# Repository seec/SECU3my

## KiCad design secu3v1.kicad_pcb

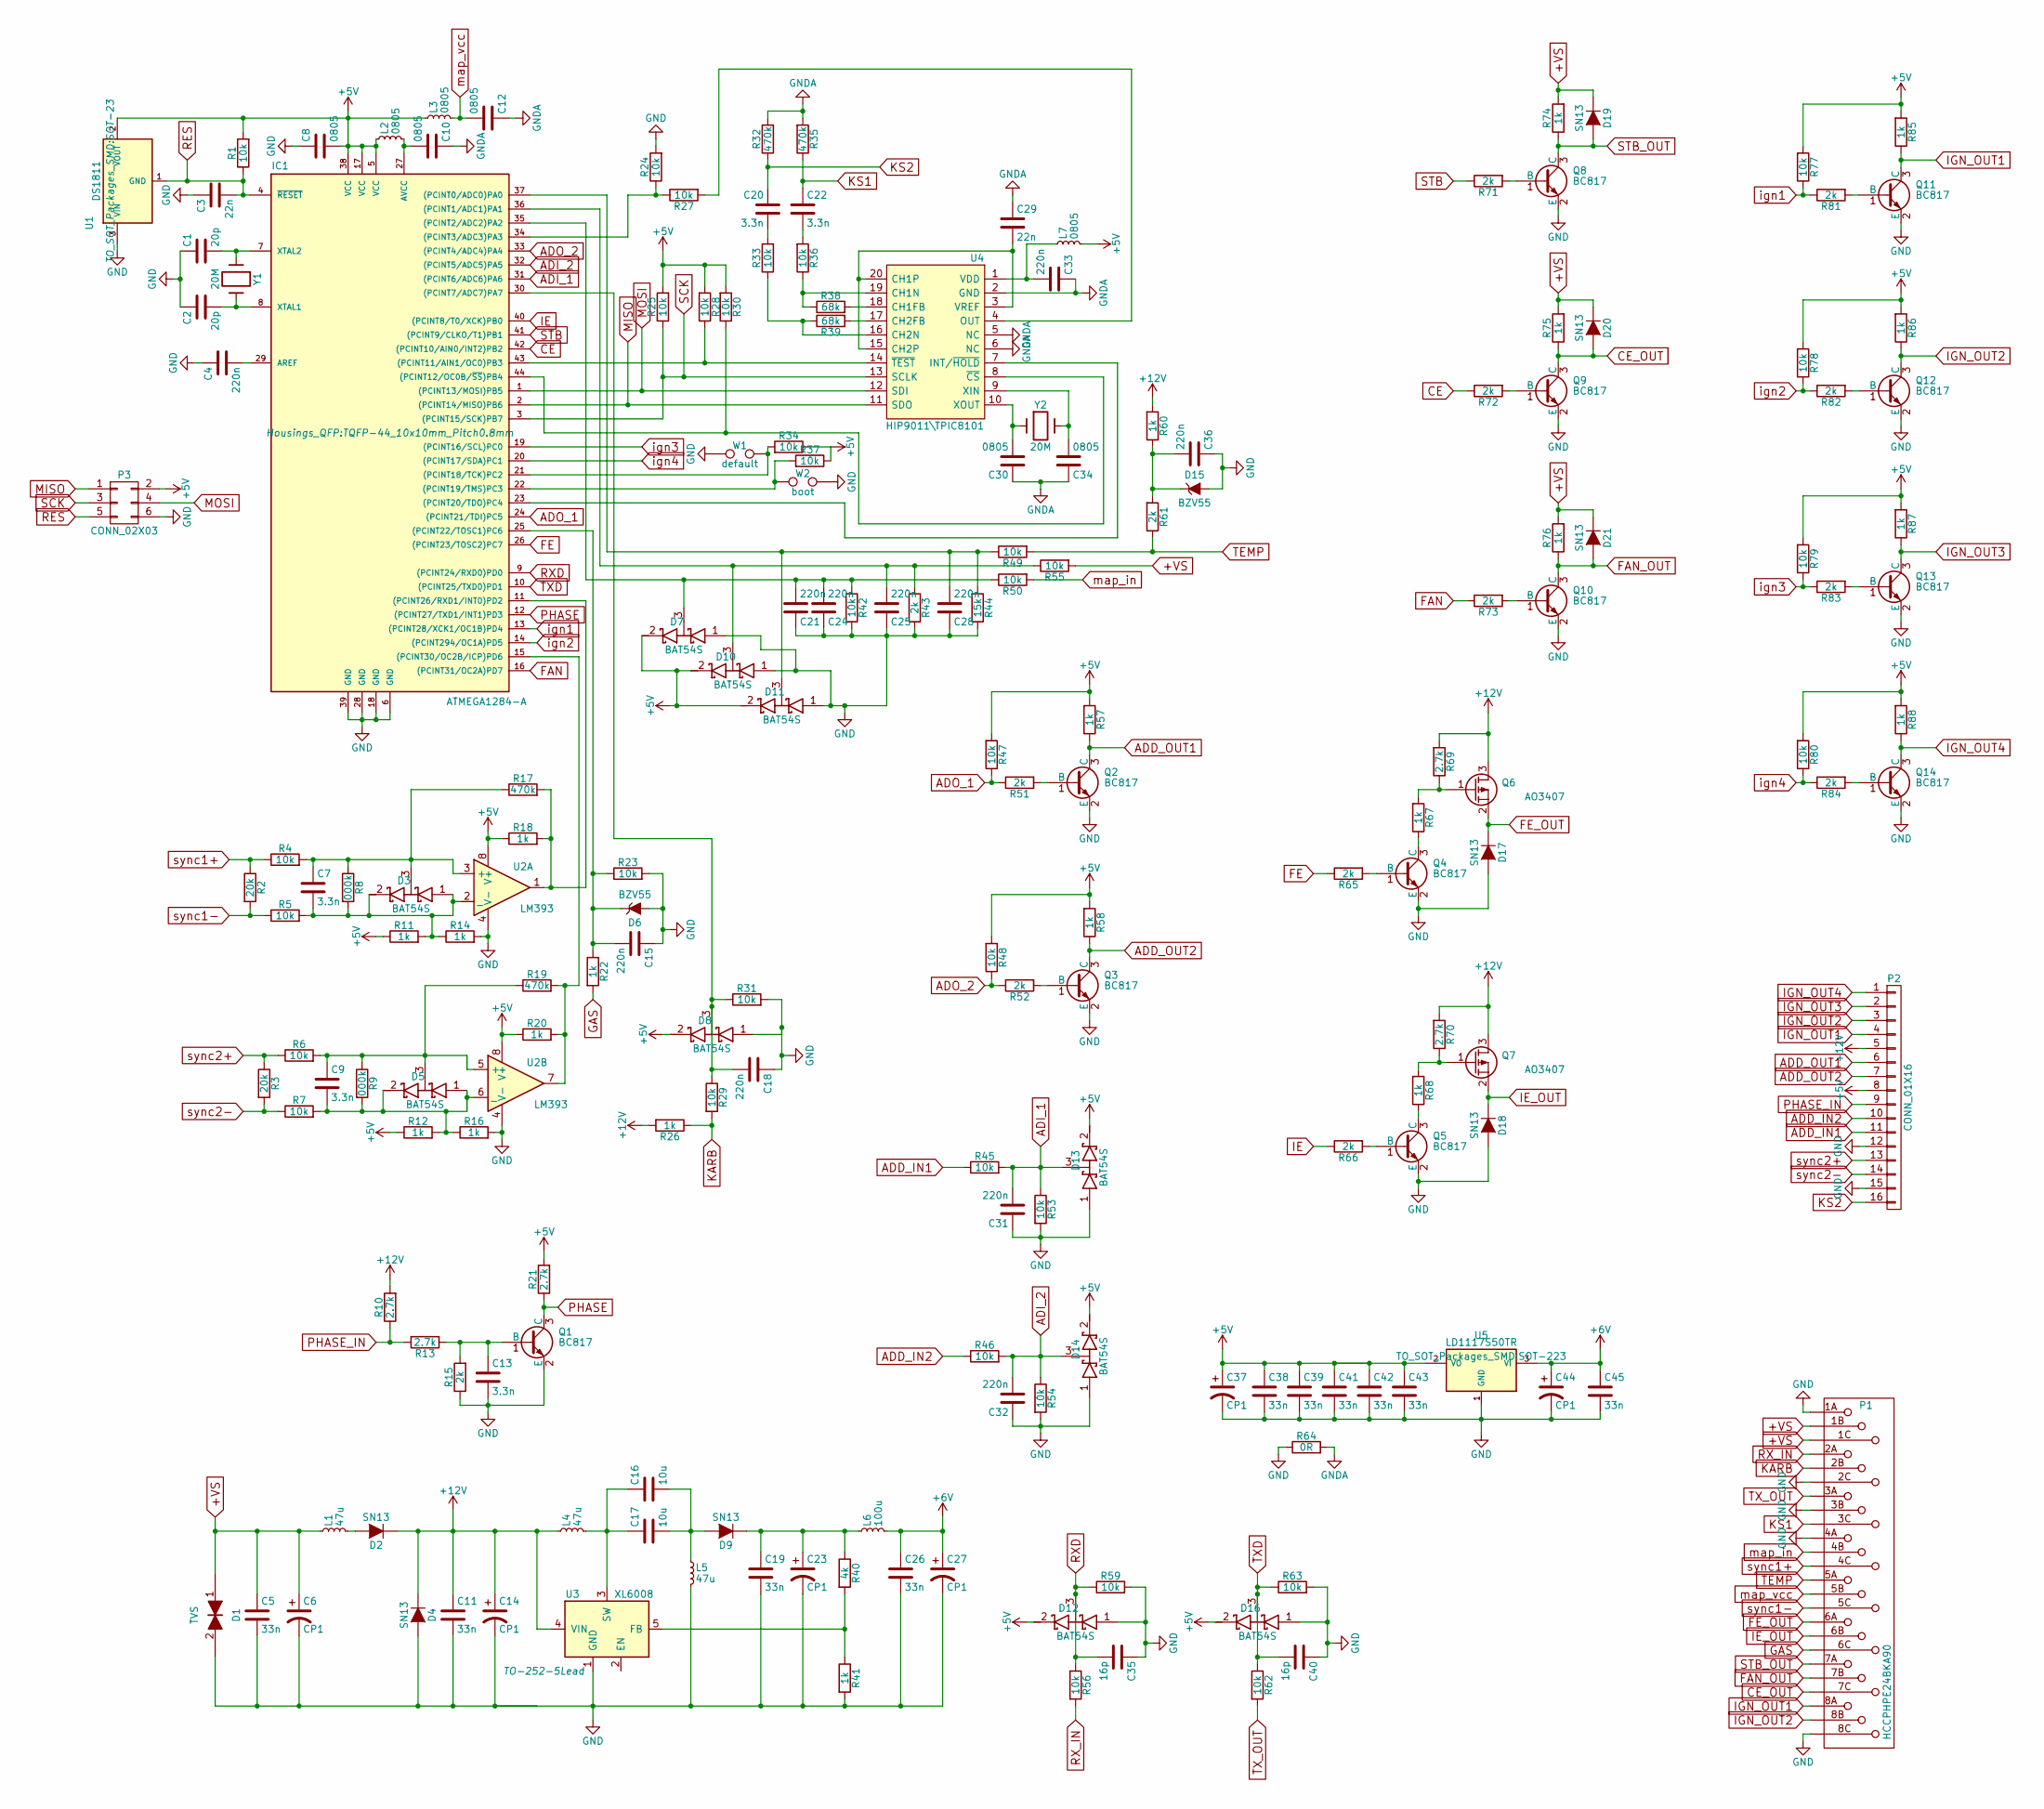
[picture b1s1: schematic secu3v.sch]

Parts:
C1, C2: 20p; C_0805
C3, C29: 22n; C_0805
C4, C15, C18, C21, C24, C25, C28, C31, C32, C33, C36: 220n; C_0805
C5, C11, C19, C26, C38, C39, C41, C42, C43, C45: 33n; C_0805
C6, C14: CP1; c_elec_8x10.5
C7, C9, C13, C20, C22: 3.3n; C_0805
C8, C10, C12, C30, C34: 0805; C_0805
C16, C17: 10u; C_0805
C23, C27, C37, C44: CP1; c_elec_6.3x4.5
C35, C40: 16p; C_0805
D1: TVS; SMA_Standard
D2, D4, D9, D17, D18, D19, D20, D21: SN13; SMA_Standard
D3, D5, D7, D8, D10, D11, D12, D13, D14, D16: BAT54S; SOT-23
D6, D15: BZV55; SMA_Standard
IC1: ATMEGA1284-A; TQFP-44_10x10mm_Pitch0.8mm
L1: 47u; Neosid_Inductor_SM-NE45_SMD1812
L2, L3, L7: 0805; Neosid_Inductor_SM-NE45_SMD1812
L4, L5: 47u; Choke_SMD_7.3x7.3_H4.5
L6: 100u; Neosid_Inductor_SM-NE45_SMD1812
P1: HCCPHPE24BKA90
P2: CONN_01X16; Pin_Header_Straight_1x16
P3: CONN_02X03; Pin_Header_Straight_2x03
Q1, Q2, Q3, Q4, Q5, Q8, Q9, Q10, Q11, Q12, Q13, Q14: BC817; SOT-23
Q6, Q7: AO3407; SOT-23
R1, R4, R5, R6, R7, R23, R24, R25, R27, R28, R29, R30, R31, R33, R34, R36, R37, R42, R45, R46, R47, R48, R49, R50, R53, R54, R55, R56, R59, R62, R63, R77, R78, R79, R80: 10k; R_0805
R2, R3: 20k; R_0805
R8, R9: 000k; R_0805
R10, R13, R21, R69, R70: 2.7k; R_0805
R11, R12, R14, R16, R18, R20, R22, R26, R41, R57, R58, R60, R67, R68, R74, R75, R76, R85, R86, R87, R88: 1k; R_0805
R15, R43, R51, R52, R61, R65, R66, R71, R72, R73, R81, R82, R83, R84: 2k; R_0805
R17, R19, R32, R35: 470k; R_0805
R38, R39: 68k; R_0805
R40: 4k; R_0805
R44: 15k; R_0805
R64: 0R; R_0805
U1: DS1811; SOT-23
U2: LM393; SOIC-8_3.9x4.9mm_Pitch1.27mm
U3: XL6008; TO-252-5Lead
U4: HIP9011\\TPIC8101; SOIC-20W_7.5x12.8mm_Pitch1.27mm
U5: LD1117S50TR; SOT-223
W1: default; Test_Point_2Pads
W2: boot; Test_Point_2Pads
Y1, Y2: 20M; Crystal_SMD_5032_2Pads

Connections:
+5V: C8.2, C37.1, C38.1, C39.1, C41.1, C42.1, C43.1, D7.2 (K), D8.2 (K), D10.2 (K), D11.2 (K), D12.2 (K), D13.2 (K), D14.2 (K), D16.2 (K), IC1.5 (VCC), IC1.17 (VCC), IC1.38 (VCC), L2.1, L3.1, L7.2, P2.8, P3.2, R1.2, R11.1, R12.1, R18.1, R20.1, R21.2, R25.2, R28.2, R30.2, R34.1, R37.1, R47.2, R48.2, R57.2, R58.2, R77.2, R78.2, R79.2, R80.2, R85.2, R86.2, R87.2, R88.2, U1.2 (VOUT), U2.8 (V+), U5.2 (VO)
+6V: C26.1, C27.1, C44.1, C45.1, L6.2, U5.3 (VI)
+12V: C11.1, C14.1, D2.1 (K), D4.1 (K), L4.1, P2.5, Q6.3 (D), Q7.3 (D), R10.2, R26.2, R60.2, R69.2, R70.2, U3.4 (VIN)
+VS: C5.1, C6.1, D1.1, D19.1 (K), D20.1 (K), D21.1 (K), L1.1, P1.1B, P1.1C, R55.2, R74.2, R75.2, R76.2
ADD_IN1: P2.11, R45.1
ADD_IN2: P2.10, R46.1
ADD_OUT1: P2.6, Q2.3 (C), R57.1
ADD_OUT2: P2.7, Q3.3 (C), R58.1
ADI_1: C31.2, D13.3 (common), IC1.31 ((PCINT6/ADC6)PA6), R45.2, R53.1
ADI_2: C32.2, D14.3 (common), IC1.32 ((PCINT5/ADC5)PA5), R46.2, R54.1
ADO_1: IC1.24 ((PCINT21/TDI)PC5), R47.1, R51.1
ADO_2: IC1.33 ((PCINT4/ADC4)PA4), R48.1, R52.1
CE: IC1.42 ((PCINT10/AIN0/INT2)PB2), R72.1
CE_OUT: D20.2 (A), P1.7C, Q9.3 (C), R75.1
FAN: IC1.16 ((PCINT31/OC2A)PD7), R73.1
FAN_OUT: D21.2 (A), P1.7B, Q10.3 (C), R76.1
FE: IC1.26 ((PCINT23/TOSC2)PC7), R65.1
FE_OUT: D17.1 (K), P1.6A, Q6.2 (S)
GAS: P1.6C, R22.2
GND: C1.1, C2.1, C3.1, C4.1, C5.2, C6.2, C8.1, C11.2, C13.2, C14.2, C15.1, C18.1, C19.2, C21.1, C23.2, C24.1, C25.1, C26.2, C27.2, C28.1, C31.1, C32.1, C35.1, C36.1, C37.2, C38.2, C39.2, C40.1, C41.2, C42.2, C43.2, C44.2, C45.2, D1.2, D4.2 (A), D6.2 (A), D7.1 (A), D8.1 (A), D10.1 (A), D11.1 (A), D12.1 (A), D13.1 (A), D14.1 (A), D15.2 (A), D16.1 (A), D17.2 (A), D18.2 (A), IC1.6 (GND), IC1.18 (GND), IC1.28 (GND), IC1.39 (GND), L5.2, P1.1A, P1.2C, P1.3B, P1.4A, P1.8C, P2.12, P2.15, P3.6, Q1.2 (E), Q2.2 (E), Q3.2 (E), Q4.2 (E), Q5.2 (E), Q8.2 (E), Q9.2 (E), Q10.2 (E), Q11.2 (E), Q12.2 (E), Q13.2 (E), Q14.2 (E), R14.2, R15.1, R16.2, R23.2, R24.2, R31.2, R41.2, R42.1, R43.1, R44.1, R53.2, R54.2, R59.2, R63.2, R64.1, U1.3 (VIN), U2.4 (V-), U3.1 (GND), U5.1 (GND), W1.1, W2.2; also elsewhere on the board
GNDA: C10.1, C12.1, C29.1, C30.1, C33.1, C34.1, R32.2, R35.2, R64.2, U4.2 (GND), U4.5 (NC), U4.6 (NC)
IE: IC1.40 ((PCINT8/T0/XCK)PB0), R66.1
IE_OUT: D18.1 (K), P1.6B, Q7.2 (S)
IGN_OUT1: P1.8A, P2.4, Q11.3 (C), R85.1
IGN_OUT2: P1.8B, P2.3, Q12.3 (C), R86.1
IGN_OUT3: P2.2, Q13.3 (C), R87.1
IGN_OUT4: P2.1, Q14.3 (C), R88.1
KARB: P1.2B, R26.1, R29.2
KS1: C22.1, P1.3C, R35.1
KS2: C20.1, P2.16, R32.1
MISO: IC1.2 ((PCINT14/MISO)PB6), P3.1, U4.11 (SDO)
MOSI: IC1.1 ((PCINT13/MOSI)PB5), P3.4, U4.12 (SDI)
unnamed: C1.2, IC1.7 (XTAL2), Y1.1
unnamed: C2.2, IC1.8 (XTAL1), Y1.2
unnamed: C4.2, IC1.29 (AREF)
unnamed: C7.1, D3.3 (common), R4.2, R8.1, R17.1, U2.3 (+)
unnamed: C7.2, D3.1 (A), D3.2 (K), R5.2, R8.2, R11.2, R14.1, U2.2 (_)
unnamed: C9.1, D5.3 (common), R6.2, R9.1, R19.1, U2.5 (+)
unnamed: C9.2, D5.1 (A), D5.2 (K), R7.2, R9.2, R12.2, R16.1, U2.6 (_)
unnamed: C10.2, IC1.27 (AVCC), L2.2
unnamed: C13.1, Q1.1 (B), R13.1, R15.2
unnamed: C15.2, D6.1 (K), IC1.25 ((PCINT22/TOSC1)PC6), R22.1, R23.1
unnamed: C16.1, C17.1, L4.2, U3.3 (SW)
unnamed: C16.2, C17.2, D9.2 (A), L5.1
unnamed: C18.2, D8.3 (common), IC1.30 ((PCINT7/ADC7)PA7), R29.1, R31.1
unnamed: C19.1, C23.1, D9.1 (K), L6.1, R40.1
unnamed: C20.2, R33.2
unnamed: C21.2, C24.2, D7.3 (common), IC1.35 ((PCINT2/ADC2)PA2), R42.2, R50.1
unnamed: C22.2, R36.2
unnamed: C25.2, D10.3 (common), IC1.36 ((PCINT1/ADC1)PA1), R43.2, R55.1
unnamed: C28.2, D11.3 (common), IC1.37 ((PCINT0/ADC0)PA0), R44.2, R49.1
unnamed: C29.2, U4.3 (VREF), U4.15 (CH2P), U4.20 (CH1P)
unnamed: C30.2, U4.10 (XOUT), Y2.1
unnamed: C33.2, L7.1, U4.1 (VDD)
unnamed: C34.2, U4.9 (XIN), Y2.2
unnamed: C36.2, D15.1 (K), R60.1, R61.2
unnamed: D2.2 (A), L1.2
unnamed: IC1.11 ((PCINT26/RXD1/INT0)PD2), R17.2, R18.2, U2.1
unnamed: IC1.15 ((PCINT30/OC2B/ICP)PD6), R19.2, R20.2, U2.7
unnamed: IC1.21 ((PCINT18/TCK)PC2), R34.2, W1.2
unnamed: IC1.22 ((PCINT19/TMS)PC3), R37.2, W2.1
unnamed: IC1.23 ((PCINT20/TDO)PC4), U4.7 (INT/~HOLD)
unnamed: IC1.34 ((PCINT3/ADC3)PA3), R24.1, R27.1
unnamed: IC1.43 ((PCINT11/AIN1/OC0)PB3), R28.1, U4.14 (~TEST)
unnamed: IC1.44 ((PCINT12/OC0B/~SS~)PB4), R30.1, U4.8 (~CS)
unnamed: Q2.1 (B), R51.2
unnamed: Q3.1 (B), R52.2
unnamed: Q4.1 (B), R65.2
unnamed: Q4.3 (C), R67.1
unnamed: Q5.1 (B), R66.2
unnamed: Q5.3 (C), R68.1
unnamed: Q6.1 (G), R67.2, R69.1
unnamed: Q7.1 (G), R68.2, R70.1
unnamed: Q8.1 (B), R71.2
unnamed: Q9.1 (B), R72.2
unnamed: Q10.1 (B), R73.2
unnamed: Q11.1 (B), R81.2
unnamed: Q12.1 (B), R82.2
unnamed: Q13.1 (B), R83.2
unnamed: Q14.1 (B), R84.2
unnamed: R27.2, U4.4 (OUT)
unnamed: R33.1, R39.1, U4.16 (CH2N)
unnamed: R36.1, R38.1, U4.19 (CH1N)
unnamed: R38.2, U4.18 (CH1FB)
unnamed: R39.2, U4.17 (CH2FB)
unnamed: R40.2, R41.1, U3.5 (FB)
PHASE: IC1.12 ((PCINT27/TXD1/INT1)PD3), Q1.3 (C), R21.1
PHASE_IN: P2.9, R10.1, R13.2
RES: C3.2, IC1.4 (~RESET), P3.5, R1.1, U1.1 (GND)
RXD: C35.2, D12.3 (common), IC1.9 ((PCINT24/RXD0)PD0), R56.1, R59.1
RX_IN: P1.2A, R56.2
SCK: IC1.3 ((PCINT15/SCK)PB7), P3.3, R25.1, U4.13 (SCLK)
STB: IC1.41 ((PCINT9/CLKO/T1)PB1), R71.1
STB_OUT: D19.2 (A), P1.7A, Q8.3 (C), R74.1
TEMP: P1.5A, R49.2, R61.1
TXD: C40.2, D16.3 (common), IC1.10 ((PCINT25/TXD0)PD1), R62.1, R63.1
TX_OUT: P1.3A, R62.2
ign1: IC1.13 ((PCINT28/XCK1/OC1B)PD4), R77.1, R81.1
ign2: IC1.14 ((PCINT294/OC1A)PD5), R78.1, R82.1
ign3: IC1.19 ((PCINT16/SCL)PC0), R79.1, R83.1
ign4: IC1.20 ((PCINT17/SDA)PC1), R80.1, R84.1
map_in: P1.4B, R50.2
map_vcc: C12.2, L3.2, P1.5B
sync1+: P1.4C, R2.1, R4.1
sync1-: P1.5C, R2.2, R5.1
sync2+: P2.13, R3.1, R6.1
sync2-: P2.14, R3.2, R7.1

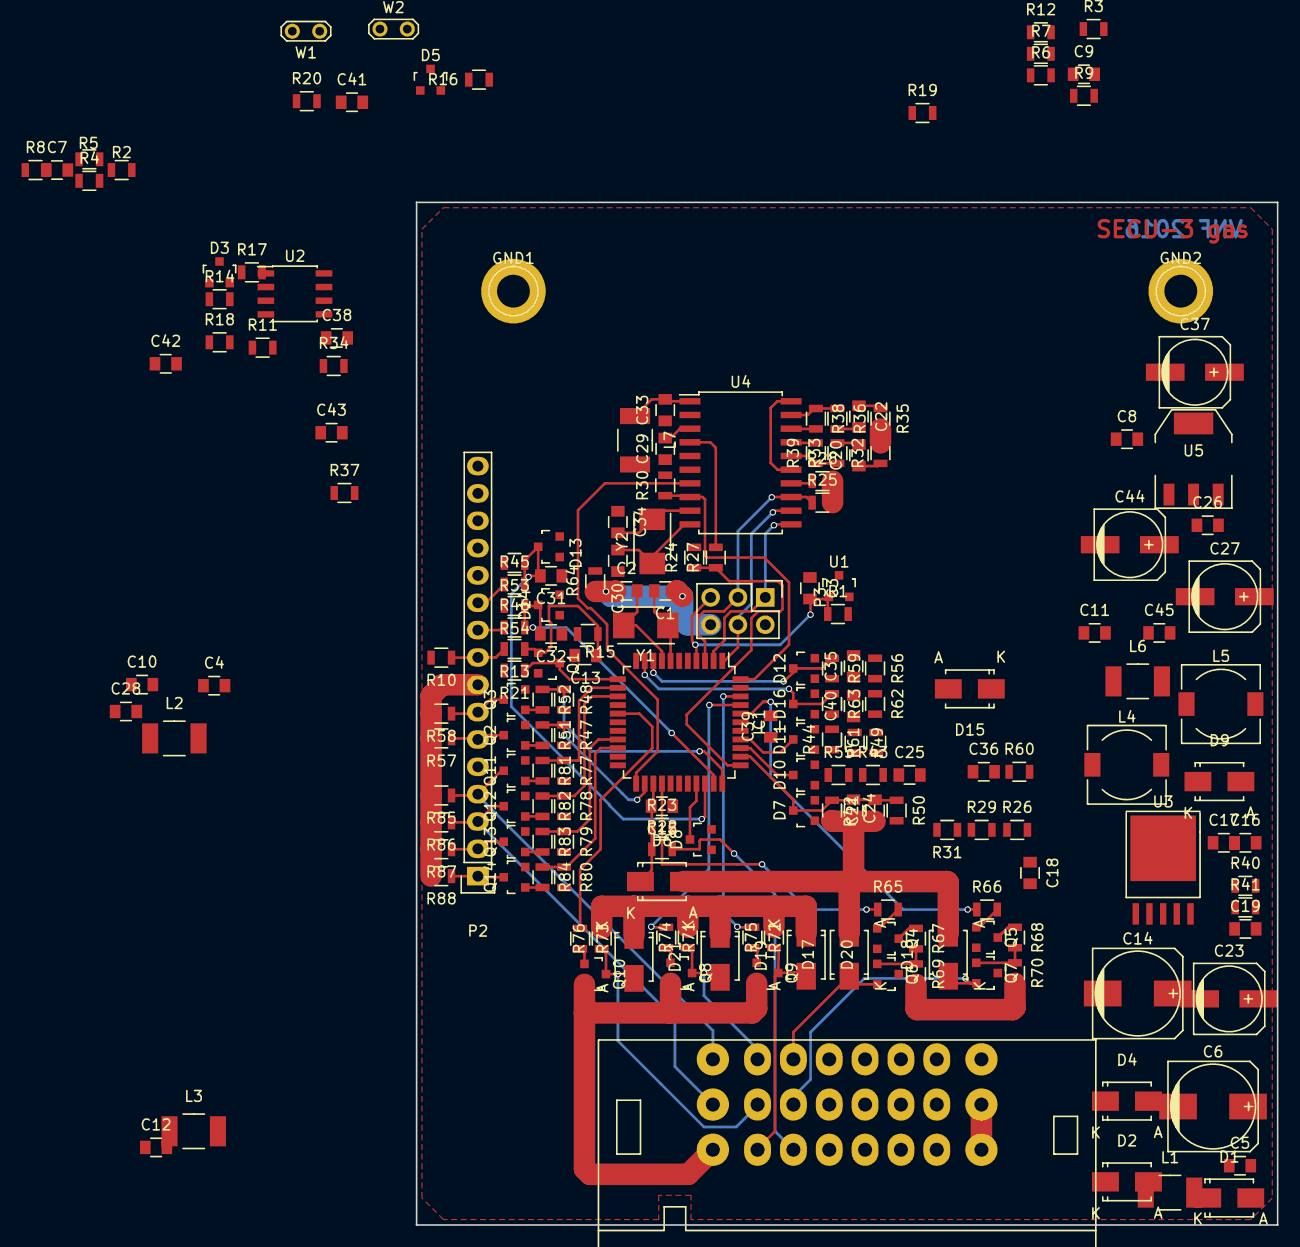
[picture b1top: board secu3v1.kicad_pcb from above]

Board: 2 copper layers, 80.0 x 95.0 mm, 190 parts (0 on the bottom side), 107 nets.

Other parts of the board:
GND1, GND2: 1pin

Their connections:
GND: GND1.1, GND2.2; also elsewhere on the board

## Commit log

2016-09-24 добавлено описание
2016-10-23 промежуточная точка - исправлено размещение отверстий и платы в корпусе
